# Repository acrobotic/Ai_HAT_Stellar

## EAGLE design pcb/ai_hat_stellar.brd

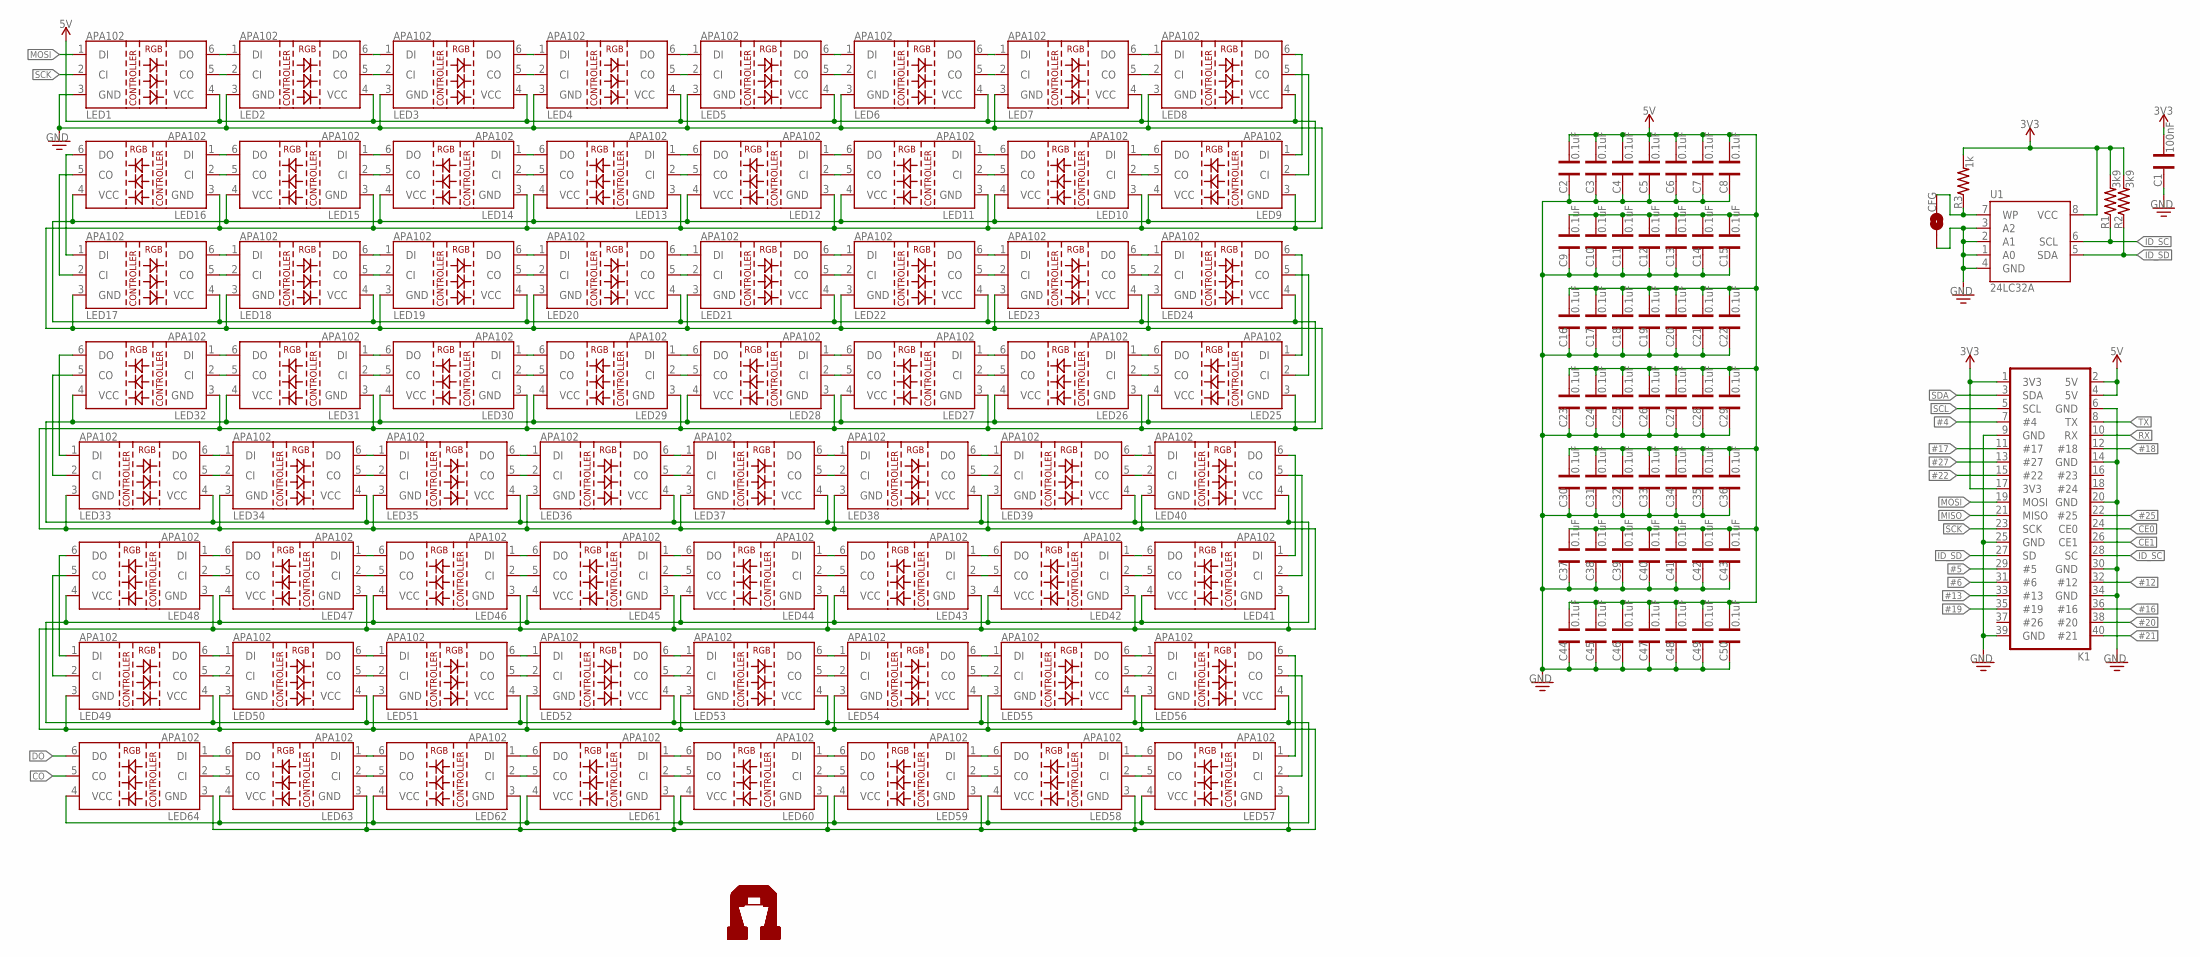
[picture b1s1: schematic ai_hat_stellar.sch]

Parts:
C1: 100nF; CAP-0603
C2, C3, C4, C5, C6, C7, C8, C9, C10, C11, C12, C13, C14, C15, C16, C17, C18, C19, C20, C21, C22, C23, C24, C25, C26, C27, C28, C29, C30, C31, C32, C33, C34, C35, C36, C37, C38, C39, C40, C41, C42, C43, C44, C45, C46, C47, C48, C49, C50: 0.1uF; CAP-0603
CFG: 1X02-SJ-NO
K1: 2X20-RPI
LED1, LED2, LED3, LED4, LED5, LED6, LED7, LED8, LED9, LED10, LED11, LED12, LED13, LED14, LED15, LED16, LED17, LED18, LED19, LED20, LED21, LED22, LED23, LED24, LED25, LED26, LED27, LED28, LED29, LED30, LED31, LED32, LED33, LED34, LED35, LED36, LED37, LED38, LED39, LED40, LED41, LED42, LED43, LED44, LED45, LED46, LED47, LED48, LED49, LED50, LED51, LED52, LED53, LED54, LED55, LED56, LED57, LED58, LED59, LED60, LED61, LED62, LED63, LED64: LED-APA102
R1, R2: 3k9; RES-0603; TOLERANCE 5%
R3: 1k; RES-0603; TOLERANCE 5%
U1: 24LC32A; SO08-EIAJ
U$9, U$10: AI-LOGOXS; AI-LOGO-XS

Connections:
3V3: C1.1, K1.1 (3V3), K1.17 (3V3), R1.2, R2.2, R3.2, U1.8 (VCC)
5V: C2.1, C3.1, C4.1, C5.1, C6.1, C7.1, C8.1, C9.1, C10.1, C11.1, C12.1, C13.1, C14.1, C15.1, C16.1, C17.1, C18.1, C19.1, C20.1, C21.1, C22.1, C23.1, C24.1, C25.1, C26.1, C27.1, C28.1, C29.1, C30.1, C31.1, C32.1, C33.1, C34.1, C35.1, C36.1, C37.1, C38.1, C39.1, C40.1, C41.1, C42.1, C43.1, C44.1, C45.1, C46.1, C47.1, C48.1, C49.1, C50.1, K1.2 (5V), K1.4 (5V), LED1.4 (VCC), LED2.4 (VCC), LED3.4 (VCC), LED4.4 (VCC), LED5.4 (VCC), LED6.4 (VCC), LED7.4 (VCC), LED8.4 (VCC), LED9.4 (VCC), LED10.4 (VCC), LED11.4 (VCC), LED12.4 (VCC), LED13.4 (VCC), LED14.4 (VCC), LED15.4 (VCC), LED16.4 (VCC), LED17.4 (VCC), LED18.4 (VCC), LED19.4 (VCC), LED20.4 (VCC), LED21.4 (VCC), LED22.4 (VCC), LED23.4 (VCC), LED24.4 (VCC), LED25.4 (VCC), LED26.4 (VCC), LED27.4 (VCC), LED28.4 (VCC), LED29.4 (VCC), LED30.4 (VCC), LED31.4 (VCC), LED32.4 (VCC), LED33.4 (VCC), LED34.4 (VCC), LED35.4 (VCC), LED36.4 (VCC), LED37.4 (VCC), LED38.4 (VCC), LED39.4 (VCC), LED40.4 (VCC), LED41.4 (VCC), LED42.4 (VCC), LED43.4 (VCC), LED44.4 (VCC), LED45.4 (VCC), LED46.4 (VCC), LED47.4 (VCC), LED48.4 (VCC), LED49.4 (VCC), LED50.4 (VCC), LED51.4 (VCC), LED52.4 (VCC), LED53.4 (VCC), LED54.4 (VCC), LED55.4 (VCC), LED56.4 (VCC), LED57.4 (VCC), LED58.4 (VCC), LED59.4 (VCC), LED60.4 (VCC), LED61.4 (VCC), LED62.4 (VCC), LED63.4 (VCC), LED64.4 (VCC)
#4: K1.7 (#4)
#5: K1.29 (#5)
#6: K1.31 (#6)
#12: K1.32 (#12)
#13: K1.33 (#13)
#16: K1.36 (#16)
#17: K1.11 (#17)
#18: K1.12 (#18)
#19: K1.35 (#19)
#20: K1.38 (#20)
#21: K1.40 (#21)
#22: K1.15 (#22)
#25: K1.22 (#25)
#27: K1.13 (#27)
CE0: K1.24 (CE0)
CE1: K1.26 (CE1)
CO: LED64.5 (CO)
DO: LED64.6 (DO)
GND: C1.2, C2.2, C3.2, C4.2, C5.2, C6.2, C7.2, C8.2, C9.2, C10.2, C11.2, C12.2, C13.2, C14.2, C15.2, C16.2, C17.2, C18.2, C19.2, C20.2, C21.2, C22.2, C23.2, C24.2, C25.2, C26.2, C27.2, C28.2, C29.2, C30.2, C31.2, C32.2, C33.2, C34.2, C35.2, C36.2, C37.2, C38.2, C39.2, C40.2, C41.2, C42.2, C43.2, C44.2, C45.2, C46.2, C47.2, C48.2, C49.2, C50.2, CFG.1, K1.6 (GND), K1.9 (GND), K1.14 (GND), K1.20 (GND), K1.25 (GND), K1.30 (GND), K1.34 (GND), K1.39 (GND), LED1.3 (GND), LED2.3 (GND), LED3.3 (GND), LED4.3 (GND), LED5.3 (GND), LED6.3 (GND), LED7.3 (GND), LED8.3 (GND), LED9.3 (GND), LED10.3 (GND), LED11.3 (GND), LED12.3 (GND), LED13.3 (GND), LED14.3 (GND), LED15.3 (GND), LED16.3 (GND), LED17.3 (GND), LED18.3 (GND), LED19.3 (GND), LED20.3 (GND), LED21.3 (GND), LED22.3 (GND), LED23.3 (GND), LED24.3 (GND), LED25.3 (GND), LED26.3 (GND), LED27.3 (GND), LED28.3 (GND), LED29.3 (GND), LED30.3 (GND), LED31.3 (GND), LED32.3 (GND), LED33.3 (GND), LED34.3 (GND), LED35.3 (GND), LED36.3 (GND), LED37.3 (GND), LED38.3 (GND), LED39.3 (GND), LED40.3 (GND), LED41.3 (GND), LED42.3 (GND), LED43.3 (GND), LED44.3 (GND), LED45.3 (GND), LED46.3 (GND), LED47.3 (GND), LED48.3 (GND), LED49.3 (GND), LED50.3 (GND), LED51.3 (GND), LED52.3 (GND), LED53.3 (GND), LED54.3 (GND), LED55.3 (GND), LED56.3 (GND), LED57.3 (GND), LED58.3 (GND), LED59.3 (GND), LED60.3 (GND), LED61.3 (GND), LED62.3 (GND), LED63.3 (GND), LED64.3 (GND), U1.1 (A0), U1.2 (A1), U1.3 (A2), U1.4 (GND)
ID_SC: K1.28 (SC), R1.1, U1.6 (SCL)
ID_SD: K1.27 (SD), R2.1, U1.5 (SDA)
MISO: K1.21 (MISO)
MOSI: K1.19 (MOSI), LED1.1 (DI)
unnamed: LED8.5 (CO), LED9.2 (CI)
unnamed: LED9.5 (CO), LED10.2 (CI)
unnamed: CFG.2, R3.1, U1.7 (WP)
unnamed: LED8.6 (DO), LED9.1 (DI)
unnamed: LED1.5 (CO), LED2.2 (CI)
unnamed: LED1.6 (DO), LED2.1 (DI)
unnamed: LED2.6 (DO), LED3.1 (DI)
unnamed: LED2.5 (CO), LED3.2 (CI)
unnamed: LED3.6 (DO), LED4.1 (DI)
unnamed: LED3.5 (CO), LED4.2 (CI)
unnamed: LED4.6 (DO), LED5.1 (DI)
unnamed: LED4.5 (CO), LED5.2 (CI)
unnamed: LED5.6 (DO), LED6.1 (DI)
unnamed: LED5.5 (CO), LED6.2 (CI)
unnamed: LED6.6 (DO), LED7.1 (DI)
unnamed: LED6.5 (CO), LED7.2 (CI)
unnamed: LED7.6 (DO), LED8.1 (DI)
unnamed: LED7.5 (CO), LED8.2 (CI)
unnamed: LED9.6 (DO), LED10.1 (DI)
unnamed: LED10.6 (DO), LED11.1 (DI)
unnamed: LED10.5 (CO), LED11.2 (CI)
unnamed: LED11.6 (DO), LED12.1 (DI)
unnamed: LED11.5 (CO), LED12.2 (CI)
unnamed: LED12.6 (DO), LED13.1 (DI)
unnamed: LED12.5 (CO), LED13.2 (CI)
unnamed: LED13.6 (DO), LED14.1 (DI)
unnamed: LED13.5 (CO), LED14.2 (CI)
unnamed: LED14.6 (DO), LED15.1 (DI)
unnamed: LED14.5 (CO), LED15.2 (CI)
unnamed: LED15.6 (DO), LED16.1 (DI)
unnamed: LED15.5 (CO), LED16.2 (CI)
unnamed: LED17.5 (CO), LED18.2 (CI)
unnamed: LED17.6 (DO), LED18.1 (DI)
unnamed: LED18.6 (DO), LED19.1 (DI)
unnamed: LED18.5 (CO), LED19.2 (CI)
unnamed: LED19.6 (DO), LED20.1 (DI)
unnamed: LED19.5 (CO), LED20.2 (CI)
unnamed: LED20.6 (DO), LED21.1 (DI)
unnamed: LED20.5 (CO), LED21.2 (CI)
unnamed: LED21.6 (DO), LED22.1 (DI)
unnamed: LED21.5 (CO), LED22.2 (CI)
unnamed: LED22.6 (DO), LED23.1 (DI)
unnamed: LED22.5 (CO), LED23.2 (CI)
unnamed: LED23.6 (DO), LED24.1 (DI)
unnamed: LED23.5 (CO), LED24.2 (CI)
unnamed: LED16.6 (DO), LED17.1 (DI)
unnamed: LED25.5 (CO), LED26.2 (CI)
unnamed: LED25.6 (DO), LED26.1 (DI)
unnamed: LED26.6 (DO), LED27.1 (DI)
unnamed: LED26.5 (CO), LED27.2 (CI)
unnamed: LED27.6 (DO), LED28.1 (DI)
unnamed: LED27.5 (CO), LED28.2 (CI)
unnamed: LED28.6 (DO), LED29.1 (DI)
unnamed: LED28.5 (CO), LED29.2 (CI)
unnamed: LED29.6 (DO), LED30.1 (DI)
unnamed: LED29.5 (CO), LED30.2 (CI)
unnamed: LED30.6 (DO), LED31.1 (DI)
unnamed: LED30.5 (CO), LED31.2 (CI)
unnamed: LED31.6 (DO), LED32.1 (DI)
unnamed: LED31.5 (CO), LED32.2 (CI)
unnamed: LED16.5 (CO), LED17.2 (CI)
unnamed: LED33.5 (CO), LED34.2 (CI)
unnamed: LED33.6 (DO), LED34.1 (DI)
unnamed: LED34.6 (DO), LED35.1 (DI)
unnamed: LED34.5 (CO), LED35.2 (CI)
unnamed: LED35.6 (DO), LED36.1 (DI)
unnamed: LED35.5 (CO), LED36.2 (CI)
unnamed: LED36.6 (DO), LED37.1 (DI)
unnamed: LED36.5 (CO), LED37.2 (CI)
unnamed: LED37.6 (DO), LED38.1 (DI)
unnamed: LED37.5 (CO), LED38.2 (CI)
unnamed: LED38.6 (DO), LED39.1 (DI)
unnamed: LED38.5 (CO), LED39.2 (CI)
unnamed: LED39.6 (DO), LED40.1 (DI)
unnamed: LED39.5 (CO), LED40.2 (CI)
unnamed: LED24.6 (DO), LED25.1 (DI)
unnamed: LED41.5 (CO), LED42.2 (CI)
unnamed: LED41.6 (DO), LED42.1 (DI)
unnamed: LED42.6 (DO), LED43.1 (DI)
unnamed: LED42.5 (CO), LED43.2 (CI)
unnamed: LED43.6 (DO), LED44.1 (DI)
unnamed: LED43.5 (CO), LED44.2 (CI)
unnamed: LED44.6 (DO), LED45.1 (DI)
unnamed: LED44.5 (CO), LED45.2 (CI)
unnamed: LED45.6 (DO), LED46.1 (DI)
unnamed: LED45.5 (CO), LED46.2 (CI)
unnamed: LED46.6 (DO), LED47.1 (DI)
unnamed: LED46.5 (CO), LED47.2 (CI)
unnamed: LED47.6 (DO), LED48.1 (DI)
unnamed: LED47.5 (CO), LED48.2 (CI)
unnamed: LED49.5 (CO), LED50.2 (CI)
unnamed: LED49.6 (DO), LED50.1 (DI)
unnamed: LED50.6 (DO), LED51.1 (DI)
unnamed: LED50.5 (CO), LED51.2 (CI)
unnamed: LED51.6 (DO), LED52.1 (DI)
unnamed: LED51.5 (CO), LED52.2 (CI)
unnamed: LED52.6 (DO), LED53.1 (DI)
unnamed: LED52.5 (CO), LED53.2 (CI)
unnamed: LED53.6 (DO), LED54.1 (DI)
unnamed: LED53.5 (CO), LED54.2 (CI)
unnamed: LED54.6 (DO), LED55.1 (DI)
unnamed: LED54.5 (CO), LED55.2 (CI)
unnamed: LED55.6 (DO), LED56.1 (DI)
unnamed: LED55.5 (CO), LED56.2 (CI)
unnamed: LED32.5 (CO), LED33.2 (CI)
unnamed: LED57.5 (CO), LED58.2 (CI)
unnamed: LED57.6 (DO), LED58.1 (DI)
unnamed: LED58.6 (DO), LED59.1 (DI)
unnamed: LED58.5 (CO), LED59.2 (CI)
unnamed: LED59.6 (DO), LED60.1 (DI)
unnamed: LED59.5 (CO), LED60.2 (CI)
unnamed: LED60.6 (DO), LED61.1 (DI)
unnamed: LED60.5 (CO), LED61.2 (CI)
unnamed: LED61.6 (DO), LED62.1 (DI)
unnamed: LED61.5 (CO), LED62.2 (CI)
unnamed: LED62.6 (DO), LED63.1 (DI)
unnamed: LED62.5 (CO), LED63.2 (CI)
unnamed: LED63.6 (DO), LED64.1 (DI)
unnamed: LED63.5 (CO), LED64.2 (CI)
unnamed: LED32.6 (DO), LED33.1 (DI)
unnamed: LED40.6 (DO), LED41.1 (DI)
unnamed: LED40.5 (CO), LED41.2 (CI)
unnamed: LED48.6 (DO), LED49.1 (DI)
unnamed: LED24.5 (CO), LED25.2 (CI)
unnamed: LED48.5 (CO), LED49.2 (CI)
unnamed: LED56.6 (DO), LED57.1 (DI)
unnamed: LED56.5 (CO), LED57.2 (CI)
RX: K1.10 (RX)
SCK: K1.23 (SCK), LED1.2 (CI)
SCL: K1.5 (SCL)
SDA: K1.3 (SDA)
TX: K1.8 (TX)

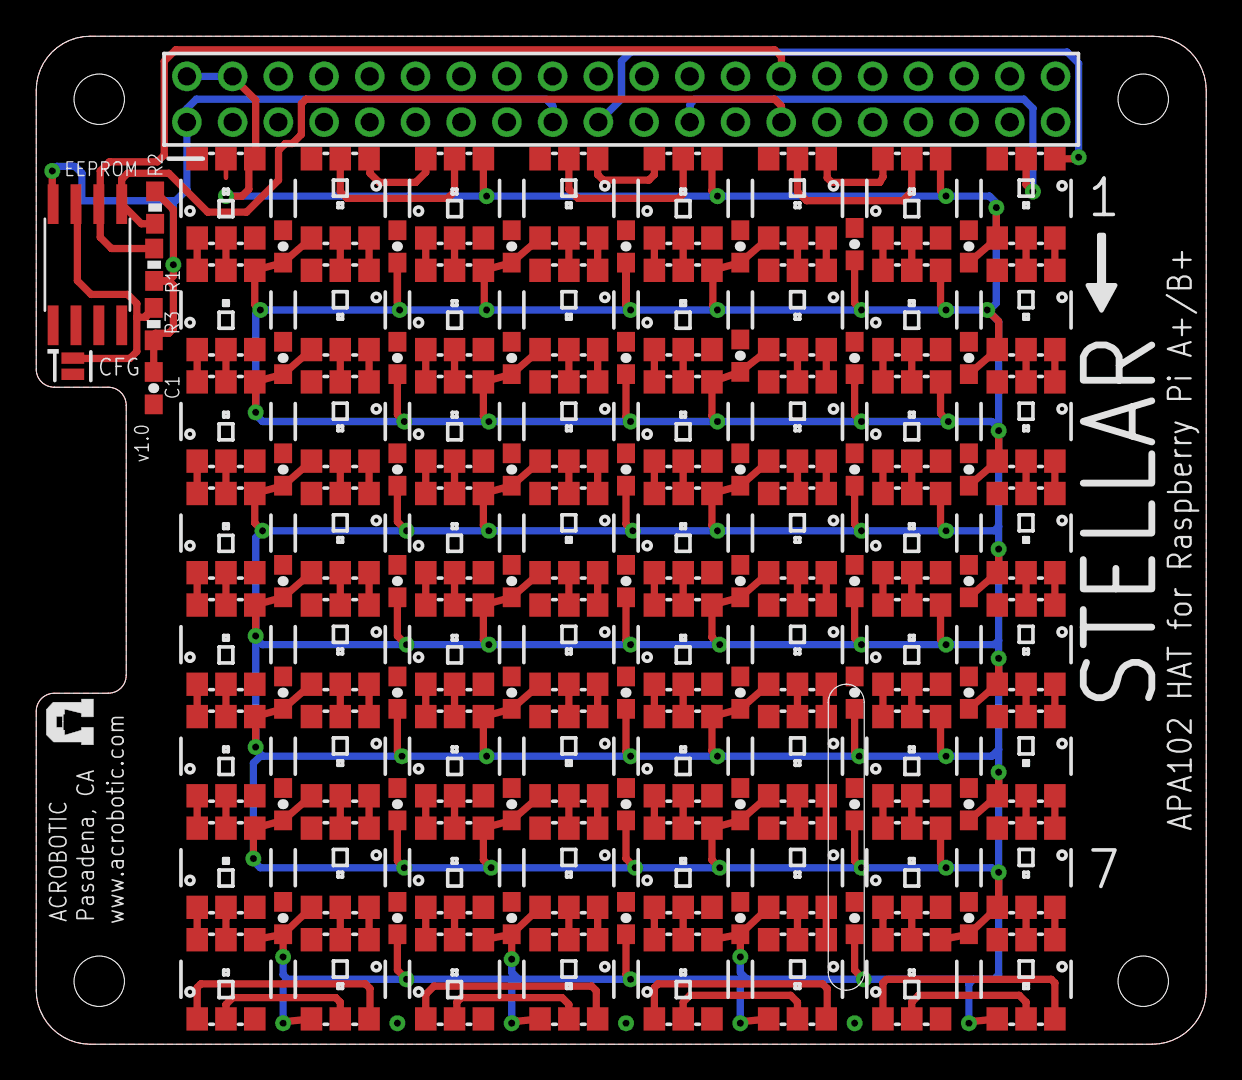
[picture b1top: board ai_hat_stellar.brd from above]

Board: 2 copper layers, 65.0 x 56.0 mm, 122 parts (1 on the bottom side), 134 nets.
